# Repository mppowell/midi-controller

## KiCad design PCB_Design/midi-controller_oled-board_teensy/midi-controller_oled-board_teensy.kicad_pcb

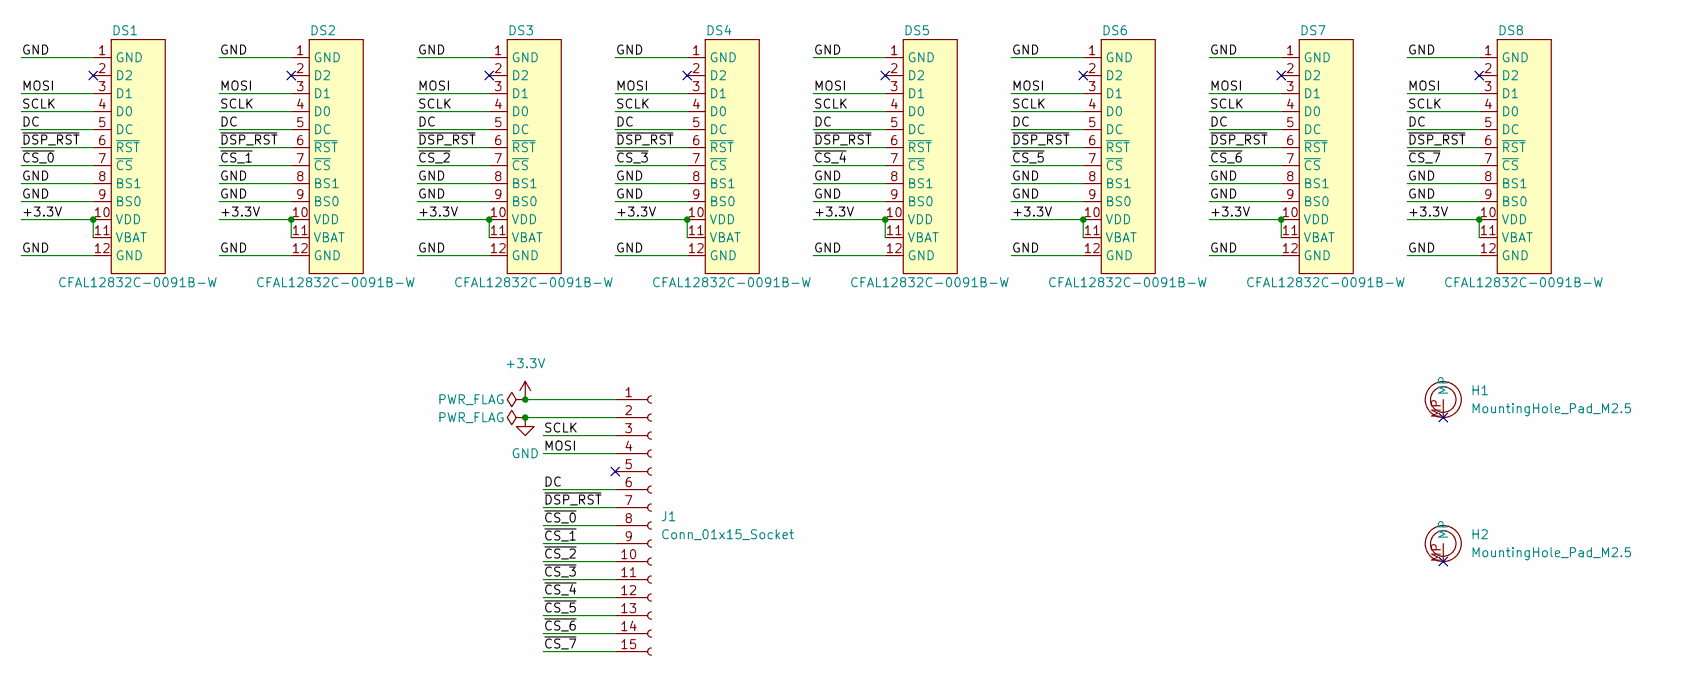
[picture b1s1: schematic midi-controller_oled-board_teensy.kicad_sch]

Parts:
DS1, DS2, DS3, DS4, DS5, DS6, DS7, DS8: CFAL12832C-0091B-W
H1, H2: MountingHole_Pad_M2.5; MountingHole_M2.5
J1: Conn_01x15_Socket; Hirose_FH12-15S-0.5SH_1x15-1MP_P0.50mm_Horizontal

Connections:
+3.3V: DS1.10 (VDD), DS1.11 (VBAT), DS2.10 (VDD), DS2.11 (VBAT), DS3.10 (VDD), DS3.11 (VBAT), DS4.10 (VDD), DS4.11 (VBAT), DS5.10 (VDD), DS5.11 (VBAT), DS6.10 (VDD), DS6.11 (VBAT), DS7.10 (VDD), DS7.11 (VBAT), DS8.10 (VDD), DS8.11 (VBAT), J1.1
/DC: DS1.5 (DC), DS2.5 (DC), DS3.5 (DC), DS4.5 (DC), DS5.5 (DC), DS6.5 (DC), DS7.5 (DC), DS8.5 (DC), J1.6
/MOSI: DS1.3 (D1), DS2.3 (D1), DS3.3 (D1), DS4.3 (D1), DS5.3 (D1), DS6.3 (D1), DS7.3 (D1), DS8.3 (D1), J1.4
/SCLK: DS1.4 (D0), DS2.4 (D0), DS3.4 (D0), DS4.4 (D0), DS5.4 (D0), DS6.4 (D0), DS7.4 (D0), DS8.4 (D0), J1.3
/~CS_0: DS1.7 (~CS), J1.8
/~CS_1: DS2.7 (~CS), J1.9
/~CS_2: DS3.7 (~CS), J1.10
/~CS_3: DS4.7 (~CS), J1.11
/~CS_4: DS5.7 (~CS), J1.12
/~CS_5: DS6.7 (~CS), J1.13
/~CS_6: DS7.7 (~CS), J1.14
/~CS_7: DS8.7 (~CS), J1.15
/~DSP_RST: DS1.6 (~RST), DS2.6 (~RST), DS3.6 (~RST), DS4.6 (~RST), DS5.6 (~RST), DS6.6 (~RST), DS7.6 (~RST), DS8.6 (~RST), J1.7
GND: DS1.1 (GND), DS1.8 (BS1), DS1.9 (BS0), DS1.12 (GND), DS2.1 (GND), DS2.8 (BS1), DS2.9 (BS0), DS2.12 (GND), DS3.1 (GND), DS3.8 (BS1), DS3.9 (BS0), DS3.12 (GND), DS4.1 (GND), DS4.8 (BS1), DS4.9 (BS0), DS4.12 (GND), DS5.1 (GND), DS5.8 (BS1), DS5.9 (BS0), DS5.12 (GND), DS6.1 (GND), DS6.8 (BS1), DS6.9 (BS0), DS6.12 (GND), DS7.1 (GND), DS7.8 (BS1), DS7.9 (BS0), DS7.12 (GND), DS8.1 (GND), DS8.8 (BS1), DS8.9 (BS0), DS8.12 (GND), J1.2

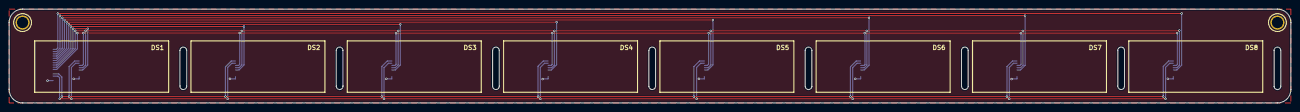
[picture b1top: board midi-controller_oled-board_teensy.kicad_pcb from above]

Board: 2 copper layers, 287.0 x 21.0 mm, 11 parts (1 on the bottom side), 14 nets.

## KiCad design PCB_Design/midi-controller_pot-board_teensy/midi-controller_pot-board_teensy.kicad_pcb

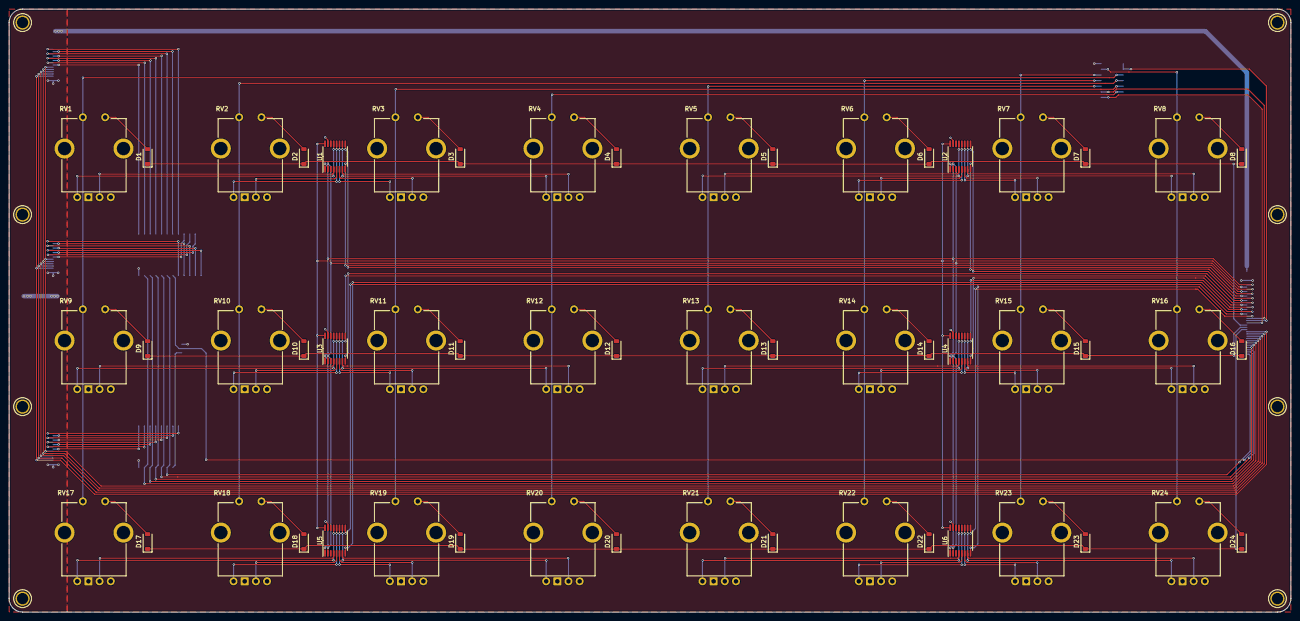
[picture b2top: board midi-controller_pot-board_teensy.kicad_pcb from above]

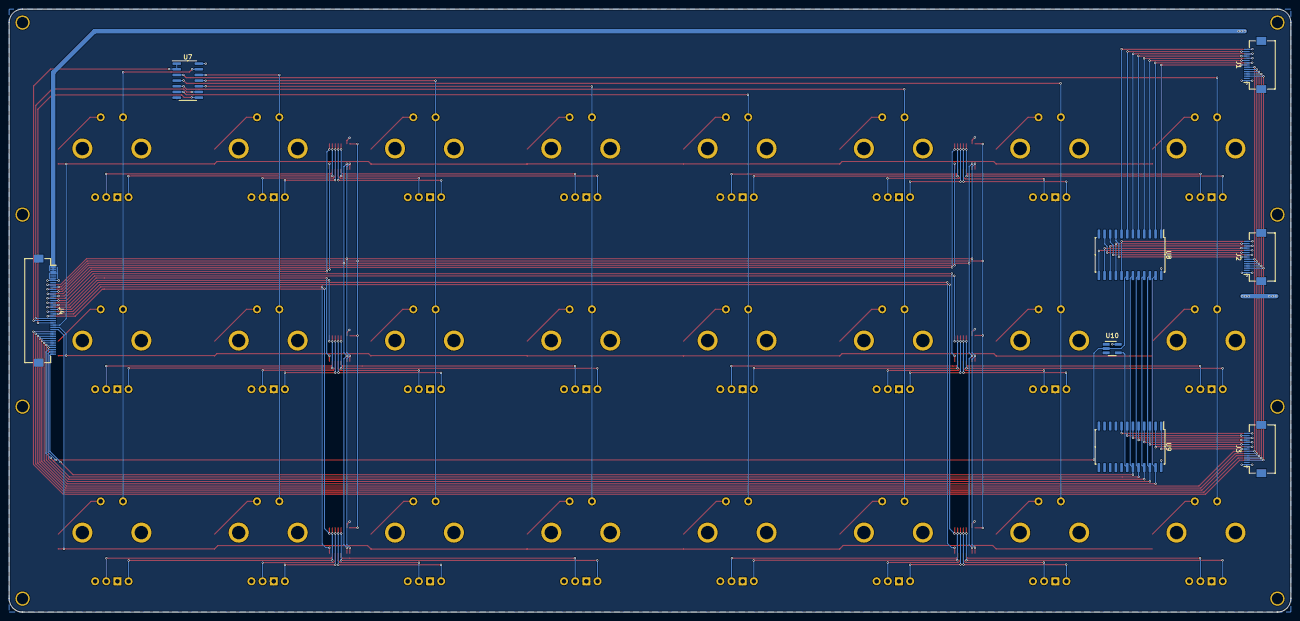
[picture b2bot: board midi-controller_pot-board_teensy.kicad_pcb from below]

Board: 2 copper layers, 287.0 x 135.0 mm, 70 parts (8 on the bottom side), 140 nets.

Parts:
D1, D2, D3, D4, D5, D6, D7, D8, D9, D10, D11, D12, D13, D14, D15, D16, D17, D18, D19, D20, D21, D22, D23, D24: D_Small_Filled; D_SOD-123
H1, H2, H3, H4, H5, H6, H7, H8: MountingHole_Pad_M2.5; MountingHole_M2.5
J1, J2, J3: Conn_01x15_Socket; Hirose_FH12-15S-0.5SH_1x15-1MP_P0.50mm_Horizontal
J4: Conn_01x40_Socket; Hirose_FH12-40S-0.5SH_1x40-1MP_P0.50mm_Horizontal
RV1, RV2, RV3, RV4, RV5, RV6, RV7, RV8, RV9, RV10, RV11, RV12, RV13, RV14, RV15, RV16, RV17, RV18, RV19, RV20, RV21, RV22, RV23, RV24: RV142FPF-40B1
U1, U2, U3, U4, U5, U6: TMUX1209_TSSOP; TSSOP-16_4.4x5mm_P0.65mm
U7: 74HC164; SO-14_3.9x8.65mm_P1.27mm
U8, U9: CD74HC154_SOIC; SOIC-24W_7.5x15.4mm_P1.27mm
U10: 74LVC1G04; SOT-23-5_HandSoldering

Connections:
+3.3V: J4.7, RV1.3 (VCC), RV2.3 (VCC), RV3.3 (VCC), RV4.3 (VCC), RV5.3 (VCC), RV6.3 (VCC), RV7.3 (VCC), RV8.3 (VCC), RV9.3 (VCC), RV10.3 (VCC), RV11.3 (VCC), RV12.3 (VCC), RV13.3 (VCC), RV14.3 (VCC), RV15.3 (VCC), RV16.3 (VCC), RV17.3 (VCC), RV18.3 (VCC), RV19.3 (VCC), RV20.3 (VCC), RV21.3 (VCC), RV22.3 (VCC), RV23.3 (VCC), RV24.3 (VCC), U1.14 (VDD), U2.14 (VDD), U3.14 (VDD), U4.14 (VDD), U5.14 (VDD), U6.14 (VDD), U7.14 (VCC), U8.24 (VCC), U9.24 (VCC), U10.5 (VCC)
+3.3VP: J1.1, J2.1, J3.1, J4.1, J4.2, J4.3
/A_{0_1}: RV1.2 (RV_1_2), U1.4 (S1A)
/A_{0_2}: RV1.4 (RV_2_2), U1.13 (S1B)
/A_{1_1}: RV2.2 (RV_1_2), U1.5 (S2A)
/A_{1_2}: RV2.4 (RV_2_2), U1.12 (S2B)
/A_{2_1}: RV3.2 (RV_1_2), U1.6 (S3A)
/A_{2_2}: RV3.4 (RV_2_2), U1.11 (S3B)
/A_{3_1}: RV4.2 (RV_1_2), U1.7 (S4A)
/A_{3_2}: RV4.4 (RV_2_2), U1.10 (S4B)
/A_{4_1}: RV5.2 (RV_1_2), U2.4 (S1A)
/A_{4_2}: RV5.4 (RV_2_2), U2.13 (S1B)
/A_{5_1}: RV6.2 (RV_1_2), U2.5 (S2A)
/A_{5_2}: RV6.4 (RV_2_2), U2.12 (S2B)
/A_{6_1}: RV7.2 (RV_1_2), U2.6 (S3A)
/A_{6_2}: RV7.4 (RV_2_2), U2.11 (S3B)
/A_{7_1}: RV8.2 (RV_1_2), U2.7 (S4A)
/A_{7_2}: RV8.4 (RV_2_2), U2.10 (S4B)
/A_{8_1}: RV9.2 (RV_1_2), U3.4 (S1A)
/A_{8_2}: RV9.4 (RV_2_2), U3.13 (S1B)
/A_{9_1}: RV10.2 (RV_1_2), U3.5 (S2A)
/A_{9_2}: RV10.4 (RV_2_2), U3.12 (S2B)
/A_{10_1}: RV11.2 (RV_1_2), U3.6 (S3A)
/A_{10_2}: RV11.4 (RV_2_2), U3.11 (S3B)
/A_{11_1}: RV12.2 (RV_1_2), U3.7 (S4A)
/A_{11_2}: RV12.4 (RV_2_2), U3.10 (S4B)
/A_{12_1}: RV13.2 (RV_1_2), U4.4 (S1A)
/A_{12_2}: RV13.4 (RV_2_2), U4.13 (S1B)
/A_{13_1}: RV14.2 (RV_1_2), U4.5 (S2A)
/A_{13_2}: RV14.4 (RV_2_2), U4.12 (S2B)
/A_{14_1}: RV15.2 (RV_1_2), U4.6 (S3A)
/A_{14_2}: RV15.4 (RV_2_2), U4.11 (S3B)
/A_{15_1}: RV16.2 (RV_1_2), U4.7 (S4A)
/A_{15_2}: RV16.4 (RV_2_2), U4.10 (S4B)
/A_{16_1}: RV17.2 (RV_1_2), U5.4 (S1A)
/A_{16_2}: RV17.4 (RV_2_2), U5.13 (S1B)
/A_{17_1}: RV18.2 (RV_1_2), U5.5 (S2A)
/A_{17_2}: RV18.4 (RV_2_2), U5.12 (S2B)
/A_{18_1}: RV19.2 (RV_1_2), U5.6 (S3A)
/A_{18_2}: RV19.4 (RV_2_2), U5.11 (S3B)
/A_{19_1}: RV20.2 (RV_1_2), U5.7 (S4A)
/A_{19_2}: RV20.4 (RV_2_2), U5.10 (S4B)
/A_{20_1}: RV21.2 (RV_1_2), U6.4 (S1A)
/A_{20_2}: RV21.4 (RV_2_2), U6.13 (S1B)
/A_{21_1}: RV22.2 (RV_1_2), U6.5 (S2A)
/A_{21_2}: RV22.4 (RV_2_2), U6.12 (S2B)
/A_{22_1}: RV23.2 (RV_1_2), U6.6 (S3A)
/A_{22_2}: RV23.4 (RV_2_2), U6.11 (S3B)
/A_{23_1}: RV24.2 (RV_1_2), U6.7 (S4A)
/A_{23_2}: RV24.4 (RV_2_2), U6.10 (S4B)
/COL_0: RV1.5 (SW_1), RV9.5 (SW_1), RV17.5 (SW_1), U7.3 (Q0)
/COL_1: RV2.5 (SW_1), RV10.5 (SW_1), RV18.5 (SW_1), U7.4 (Q1)
/COL_2: RV3.5 (SW_1), RV11.5 (SW_1), RV19.5 (SW_1), U7.5 (Q2)
/COL_3: RV4.5 (SW_1), RV12.5 (SW_1), RV20.5 (SW_1), U7.6 (Q3)
/COL_4: RV5.5 (SW_1), RV13.5 (SW_1), RV21.5 (SW_1), U7.10 (Q4)
/COL_5: RV6.5 (SW_1), RV14.5 (SW_1), RV22.5 (SW_1), U7.11 (Q5)
/COL_6: RV7.5 (SW_1), RV15.5 (SW_1), RV23.5 (SW_1), U7.12 (Q6)
/COL_7: RV8.5 (SW_1), RV16.5 (SW_1), RV24.5 (SW_1), U7.13 (Q7)
/CS_0: J4.35, U8.23 (A0), U9.23 (A0)
/CS_1: J4.36, U8.22 (A1), U9.22 (A1)
/CS_2: J4.37, U8.21 (A2), U9.21 (A2)
/CS_3: J4.38, U8.20 (A3), U9.20 (A3)
/CS_4: J4.39, U8.18 (~E1), U10.2
/CS_EN: J4.40, U8.19 (~E2), U9.19 (~E2)
/DC: J1.6, J2.6, J3.6, J4.33
/DSP_0_CS: J1.8, U8.1 (~Y0)
/DSP_1_CS: J1.9, U8.2 (~Y1)
/DSP_2_CS: J1.10, U8.3 (~Y2)
/DSP_3_CS: J1.11, U8.4 (~Y3)
/DSP_4_CS: J1.12, U8.5 (~Y4)
/DSP_5_CS: J1.13, U8.6 (~Y5)
/DSP_6_CS: J1.14, U8.7 (~Y6)
/DSP_7_CS: J1.15, U8.8 (~Y7)
/DSP_8_CS: J2.8, U8.9 (~Y8)
/DSP_9_CS: J2.9, U8.10 (~Y9)
/DSP_10_CS: J2.10, U8.11 (~Y10)
/DSP_11_CS: J2.11, U8.13 (~Y11)
/DSP_12_CS: J2.12, U8.14 (~Y12)
/DSP_13_CS: J2.13, U8.15 (~Y13)
/DSP_14_CS: J2.14, U8.16 (~Y14)
/DSP_15_CS: J2.15, U8.17 (~Y15)
/DSP_16_CS: J3.8, U9.1 (~Y0)
/DSP_17_CS: J3.9, U9.2 (~Y1)
/DSP_18_CS: J3.10, U9.3 (~Y2)
/DSP_19_CS: J3.11, U9.4 (~Y3)
/DSP_20_CS: J3.12, U9.5 (~Y4)
/DSP_21_CS: J3.13, U9.6 (~Y5)
/DSP_22_CS: J3.14, U9.7 (~Y6)
/DSP_23_CS: J3.15, U9.8 (~Y7)
/KEY_CLK: J4.26, U7.8 (CP)
/KEY_SER: J4.25, U7.1 (DSA), U7.2 (DSB)
/MISO: J1.5, J2.5, J3.5, J4.32
/MOSI: J1.4, J2.4, J3.4, J4.31
/POT_SEL_0: J4.9, U1.1 (A0), U2.1 (A0), U3.1 (A0), U4.1 (A0), U5.1 (A0), U6.1 (A0)
/POT_SEL_1: J4.10, U1.16 (A1), U2.16 (A1), U3.16 (A1), U4.16 (A1), U5.16 (A1), U6.16 (A1)
/POT_SEL_EN: J4.11, U1.2 (EN), U2.2 (EN), U3.2 (EN), U4.2 (EN), U5.2 (EN), U6.2 (EN)
/POT_{0_1}: J4.12, U1.8 (DA)
/POT_{0_2}: J4.13, U1.9 (DB)
/POT_{1_1}: J4.14, U2.8 (DA)
/POT_{1_2}: J4.15, U2.9 (DB)
/POT_{2_1}: J4.16, U3.8 (DA)
/POT_{2_2}: J4.17, U3.9 (DB)
/POT_{3_1}: J4.18, U4.8 (DA)
/POT_{3_2}: J4.19, U4.9 (DB)
/POT_{4_1}: J4.20, U5.8 (DA)
/POT_{4_2}: J4.21, U5.9 (DB)
/POT_{5_1}: J4.22, U6.8 (DA)
/POT_{5_2}: J4.23, U6.9 (DB)
/ROW_1: D1.1 (K), D2.1 (K), D3.1 (K), D4.1 (K), D5.1 (K), D6.1 (K), D7.1 (K), D8.1 (K), J4.27
/ROW_2: D9.1 (K), D10.1 (K), D11.1 (K), D12.1 (K), D13.1 (K), D14.1 (K), D15.1 (K), D16.1 (K), J4.28
/ROW_3: D17.1 (K), D18.1 (K), D19.1 (K), D20.1 (K), D21.1 (K), D22.1 (K), D23.1 (K), D24.1 (K), J4.29
/SCLK: J1.3, J2.3, J3.3, J4.30
/~KEY_CLEAR: J4.24, U7.9 (~MR)
/~OLED_RST: J1.7, J2.7, J3.7, J4.34
GND: J1.2, J2.2, J3.2, J4.4, J4.5, J4.6, J4.8, RV1.1 (GND), RV2.1 (GND), RV3.1 (GND), RV4.1 (GND), RV5.1 (GND), RV6.1 (GND), RV7.1 (GND), RV8.1 (GND), RV9.1 (GND), RV10.1 (GND), RV11.1 (GND), RV12.1 (GND), RV13.1 (GND), RV14.1 (GND), RV15.1 (GND), RV16.1 (GND), RV17.1 (GND), RV18.1 (GND), RV19.1 (GND), RV20.1 (GND), RV21.1 (GND), RV22.1 (GND), RV23.1 (GND), RV24.1 (GND), U1.15 (GND), U2.15 (GND), U3.15 (GND), U4.15 (GND), U5.15 (GND), U6.15 (GND), U7.7 (GND), U8.12 (GND), U9.12 (GND), U10.3 (GND)
unnamed: D1.2 (A), RV1.6 (SW_2)
unnamed: D2.2 (A), RV2.6 (SW_2)
unnamed: D3.2 (A), RV3.6 (SW_2)
unnamed: D4.2 (A), RV4.6 (SW_2)
unnamed: D5.2 (A), RV5.6 (SW_2)
unnamed: D6.2 (A), RV6.6 (SW_2)
unnamed: D7.2 (A), RV7.6 (SW_2)
unnamed: D8.2 (A), RV8.6 (SW_2)
unnamed: D9.2 (A), RV9.6 (SW_2)
unnamed: D10.2 (A), RV10.6 (SW_2)
unnamed: D11.2 (A), RV11.6 (SW_2)
unnamed: D12.2 (A), RV12.6 (SW_2)
unnamed: D13.2 (A), RV13.6 (SW_2)
unnamed: D14.2 (A), RV14.6 (SW_2)
unnamed: D15.2 (A), RV15.6 (SW_2)
unnamed: D16.2 (A), RV16.6 (SW_2)
unnamed: D17.2 (A), RV17.6 (SW_2)
unnamed: D18.2 (A), RV18.6 (SW_2)
unnamed: D19.2 (A), RV19.6 (SW_2)
unnamed: D20.2 (A), RV20.6 (SW_2)
unnamed: D21.2 (A), RV21.6 (SW_2)
unnamed: D22.2 (A), RV22.6 (SW_2)
unnamed: D23.2 (A), RV23.6 (SW_2)
unnamed: D24.2 (A), RV24.6 (SW_2)
unnamed: U9.18 (~E1), U10.4

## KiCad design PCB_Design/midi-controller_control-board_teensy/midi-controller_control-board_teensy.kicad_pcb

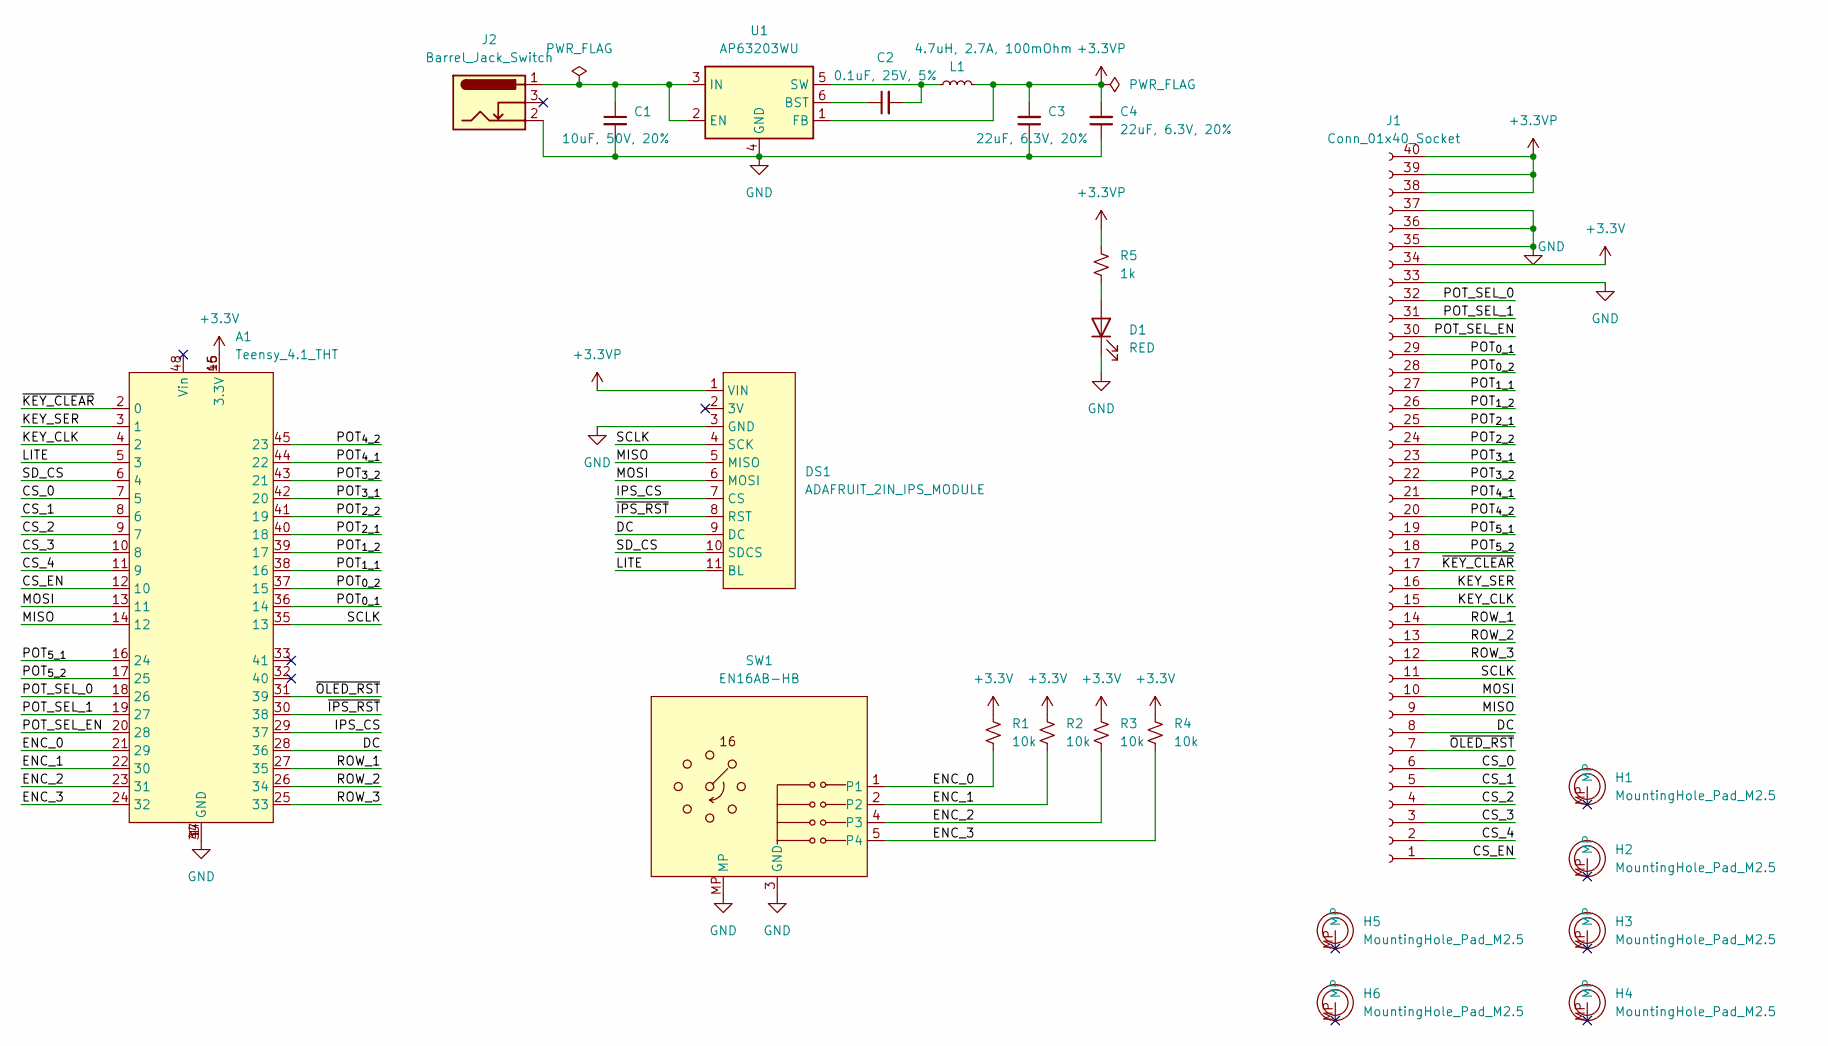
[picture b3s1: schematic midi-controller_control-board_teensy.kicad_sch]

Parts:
A1: Teensy_4.1_THT
C1: 10uF, 50V, 20%; C_1210_3225Metric_Pad1.33x2.70mm_HandSolder
C2: 0.1uF, 25V, 5%; C_0805_2012Metric_Pad1.18x1.45mm_HandSolder
C3, C4: 22uF, 6.3V, 20%; C_0805_2012Metric_Pad1.18x1.45mm_HandSolder
D1: RED; LED_0805_2012Metric_Pad1.15x1.40mm_HandSolder
DS1: ADAFRUIT_2IN_IPS_MODULE
H1, H2, H3, H4, H5, H6: MountingHole_Pad_M2.5; MountingHole_M2.5
J1: Conn_01x40_Socket; Hirose_FH12-40S-0.5SH_1x40-1MP_P0.50mm_Horizontal
J2: Barrel_Jack_Switch; BarrelJack_Horizontal
L1: 4.7uH, 2.7A, 100mOhm; L_Taiyo-Yuden_NR-60xx_HandSoldering
R1, R2, R3, R4: 10k; R_0805_2012Metric_Pad1.20x1.40mm_HandSolder
R5: 1k; R_0805_2012Metric_Pad1.20x1.40mm_HandSolder
SW1: EN16AB-HB
U1: AP63203WU; TSOT-23-6

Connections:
+3.3V: A1.15 (3.3V), A1.46 (3.3V), J1.34, R1.1, R2.1, R3.1, R4.1
+3.3VP: C3.2, C4.2, DS1.1 (VIN), J1.38, J1.39, J1.40, L1.2, R5.1, U1.1 (FB)
/CS_0: A1.7 (5), J1.6
/CS_1: A1.8 (6), J1.5
/CS_2: A1.9 (7), J1.4
/CS_3: A1.10 (8), J1.3
/CS_4: A1.11 (9), J1.2
/CS_EN: A1.12 (10), J1.1
/DC: A1.28 (36), DS1.9 (DC), J1.8
/ENC_0: A1.21 (29), R1.2, SW1.1
/ENC_1: A1.22 (30), R2.2, SW1.2
/ENC_2: A1.23 (31), R3.2, SW1.4 (P3)
/ENC_3: A1.24 (32), R4.2, SW1.5 (P4)
/IPS_CS: A1.29 (37), DS1.7 (CS)
/KEY_CLK: A1.4 (2), J1.15
/KEY_SER: A1.3 (1), J1.16
/LITE: A1.5 (3), DS1.11 (BL)
/MISO: A1.14 (12), DS1.5 (MISO), J1.9
/MOSI: A1.13 (11), DS1.6 (MOSI), J1.10
/POT_SEL_0: A1.18 (26), J1.32
/POT_SEL_1: A1.19 (27), J1.31
/POT_SEL_EN: A1.20 (28), J1.30
/POT_{0_1}: A1.36 (14), J1.29
/POT_{0_2}: A1.37 (15), J1.28
/POT_{1_1}: A1.38 (16), J1.27
/POT_{1_2}: A1.39 (17), J1.26
/POT_{2_1}: A1.40 (18), J1.25
/POT_{2_2}: A1.41 (19), J1.24
/POT_{3_1}: A1.42 (20), J1.23
/POT_{3_2}: A1.43 (21), J1.22
/POT_{4_1}: A1.44 (22), J1.21
/POT_{4_2}: A1.45 (23), J1.20
/POT_{5_1}: A1.16 (24), J1.19
/POT_{5_2}: A1.17 (25), J1.18
/ROW_1: A1.27 (35), J1.14
/ROW_2: A1.26 (34), J1.13
/ROW_3: A1.25 (33), J1.12
/SCLK: A1.35 (13), DS1.4 (SCK), J1.11
/SD_CS: A1.6 (4), DS1.10 (SDCS)
/~IPS_RST: A1.30 (38), DS1.8 (RST)
/~KEY_CLEAR: A1.2 (0), J1.17
/~OLED_RST: A1.31 (39), J1.7
GND: A1.1 (GND), A1.34 (GND), A1.47 (GND), C1.2, C3.1, C4.1, D1.1 (K), DS1.3 (GND), J1.33, J1.35, J1.36, J1.37, J2.2, SW1.3 (GND), SW1.MP, U1.4 (GND)
unnamed: D1.2 (A), R5.2
unnamed: C2.1, U1.6 (BST)
unnamed: C1.1, J2.1, U1.2 (EN), U1.3 (IN)
unnamed: C2.2, L1.1, U1.5 (SW)

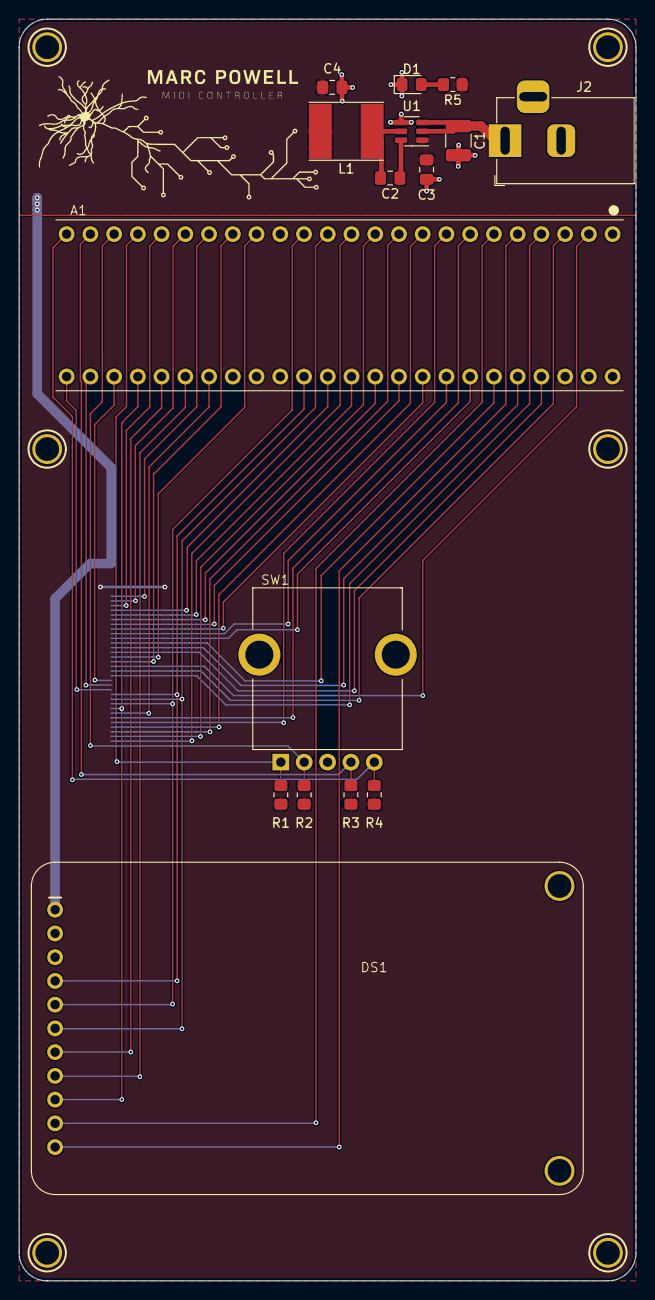
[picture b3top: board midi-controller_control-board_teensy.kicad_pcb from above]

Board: 2 copper layers, 66.0 x 135.0 mm, 23 parts (1 on the bottom side), 47 nets.

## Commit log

2023-08-27 Uploaded test arduino code developed for potentiometers
2023-08-27 Removed redundant file
2023-08-28 Got arduino talking to lightroom with one encoder
2024-06-23 Finished circuit design and initial firmware for Teensy
2024-08-12 Resolves bug when connecting more than one OLED version 2 board
    Fixes: #2
2024-09-17 Fully configured for use with Lightroom and MIDI2LR
2024-09-17 Added an "off" position for the encoder to turn off the OLED screens and IPS display when not in use
